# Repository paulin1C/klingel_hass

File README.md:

# klingel_hass
PCB and code for a small board that intercepts the bell wiring and allows muting and remote door opening with home assistant.
<br>
## hardware
### PCB
The gerber and drill files can be found in the `kicad` folder.<br>

### bill of materials
The following parts are used to assemble the PCB:
|reference|part name|value|package|
|---|---|---|---|
|C1-C5|capacitor|10 µF|smd 0805|
|D3,D4|bridge rectifier|ABS10|smd|
|D5,D11|red led||smd 0805|
|D1,D2,D6|diode|1N4007|tht DO-41|
|D7-D10|ws2812 led||smd|
|J1,J3|screw terminal|3 pins|tht 5.08 mm spacing|
|J2,J4,J5,J6|screw terminal|2 pins|tht 5.08 mm spacing|
|K1-K3|relay|5V SPDT|tht|
|Q1-Q3|transistor|BC547|tht TO-92|
|R2,R7,R8,R9,R12|resistor|1K|smd 0805|
|R1,R3,R4|resistor|10K|smd 0805|
|R5,R6|resistor|5|smd 0805|
|U1,U2|voltage regulator|AMS1117-1.5|smd SOT-223-3|
|U3|WEMOS D1 mini||tht|
|U4,U5|optocoupler|PC817|tht|

### connections
If you want to use the muting feature, you will have to cut the wires to your bell.
The voltage of your bell should be between 4V and 16V AC or DC.
A door opener could be connected to one of the relays.
|terminal name|description|
|----|----|
|5V|your 5V power supply (min. 1A)|
|bell-in|wires that normally supply power to your bell|
|bell-out|wires going to your bell|
|sense|additional input to detect voltage (4-16V AC or DC)|
|relayA,B|relay (NC = normally closes, NO = normally open)|

## software
I used esphome as a simple way to use the device with home assistant.

### configuration
Just change into the esphome directory, copy `secrets_example.yaml` to `secrets.yaml` and change its options accordingly.

### firmware upload
The firmware needs to be compiled with `esphome klingel_hass.yaml compile` and uploaded to a connected WEMOS D1 mini board with `esphome klingel_hass.yaml upload`.

### auto mute
A friend was worried about what would happen, when the device looses connection or gets stuck in a boot loop, while the bell was muted. So when auto mute is enabled, the bell stays connected/unmuted until a ring is detected and is only separating the bell connection, when the bell should be ringing. Depending on your bell, you might still hear a short ring until the relay opens.

## home assistant
The device should connect to wifi and be discovered by home assistant, which will ask you for the api password in `esphome/secrets.yaml` to connect.
<br>

### entities
|name|description|
|---|---|
|bell|changes to `on` when the bell is or should be ringing|
|sense|changes to `on` when a voltage is detected on the sense input|
|mute|mutes the bell when switched on|
|relayA|controls relay A|
|relayB|controls relay B|
|auto mute|controls auto mute feature|
|led|controls the small red led on the left|
|ws28|should control the ws2812 leds (untested)|

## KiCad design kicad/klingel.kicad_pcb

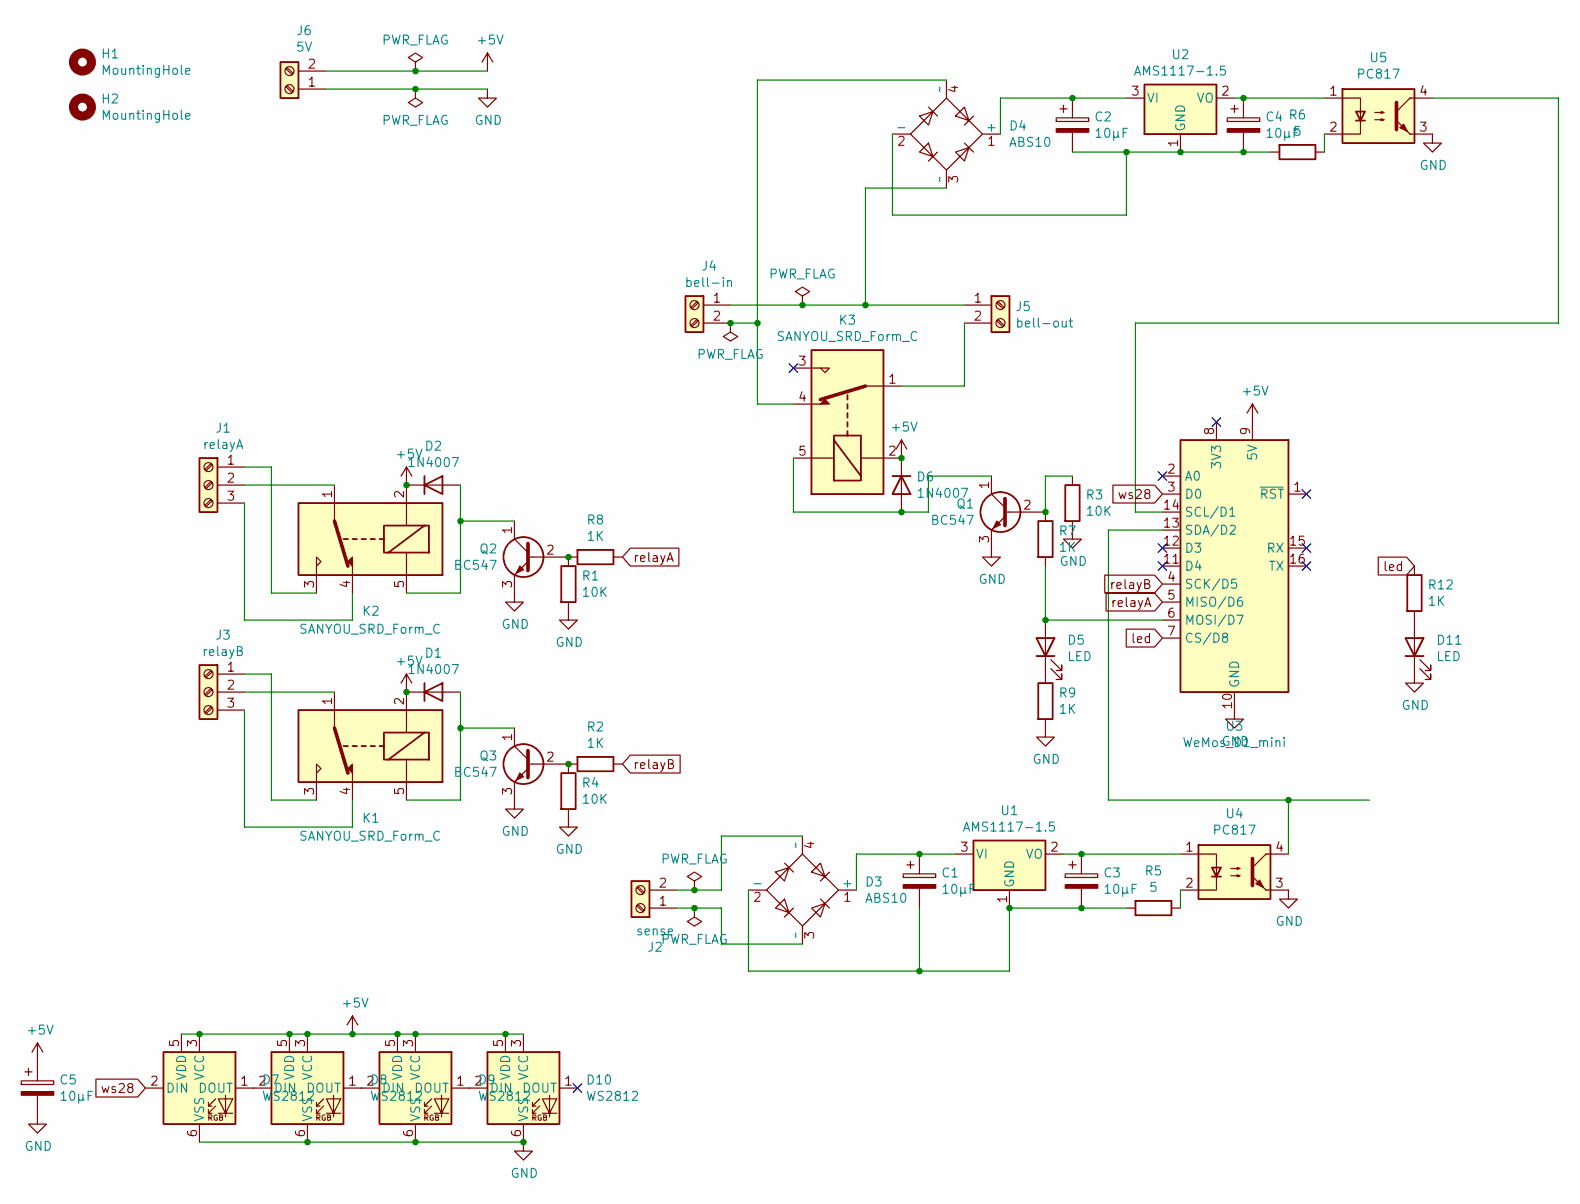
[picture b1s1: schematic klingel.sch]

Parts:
C1, C2, C3, C4, C5: 10µF; CP_EIA-3216-18_Kemet-A_Pad1.58x1.35mm_HandSolder
D1, D2, D6: 1N4007; D_DO-41_SOD81_P10.16mm_Horizontal
D3, D4: ABS10; Diode_Bridge_Diotec_ABS
D5, D11: LED; LED_0805_2012Metric
D7, D8, D9, D10: WS2812; LED_WS2812_PLCC6_5.0x5.0mm_P1.6mm
H1, H2: MountingHole; MountingHole_4.3mm_M4
J1: relayA; terminal_3pin
J2: sense; termina_2pin
J3: relayB; terminal_3pin
J4: bell-in; termina_2pin
J5: bell-out; termina_2pin
J6: 5V; termina_2pin
K1, K2, K3: SANYOU_SRD_Form_C; Relay_SPDT_SANYOU_SRD_Series_Form_C
Q1, Q2, Q3: BC547; TO-92_Inline
R1, R3, R4: 10K; R_0805_2012Metric_Pad1.20x1.40mm_HandSolder
R2, R7, R8, R9, R12: 1K; R_0805_2012Metric_Pad1.20x1.40mm_HandSolder
R5, R6: 5; R_0805_2012Metric_Pad1.20x1.40mm_HandSolder
U1, U2: AMS1117-1.5; SOT-223-3_TabPin2
U3: WeMos_D1_mini; WEMOS_D1_mini_light
U4, U5: PC817; DIP-4_W7.62mm

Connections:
+5V: C5.1, D1.1 (K), D2.1 (K), D6.1 (K), D7.3 (VCC), D7.5 (VDD), D8.3 (VCC), D8.5 (VDD), D9.3 (VCC), D9.5 (VDD), D10.3 (VCC), D10.5 (VDD), J6.2, K1.2, K2.2, K3.2, U3.9 (5V)
GND: C5.2, D7.6 (VSS), D8.6 (VSS), D9.6 (VSS), D10.6 (VSS), D11.1 (K), J6.1, Q1.3 (E), Q2.3 (E), Q3.3 (E), R1.2, R3.2, R4.2, R9.2, U3.10 (GND), U4.3, U5.3
unnamed: C1.1, D3.1 (+), U1.3 (VI)
unnamed: C1.2, C3.2, D3.2 (-), R5.2, U1.1 (GND)
unnamed: C2.1, D4.1 (+), U2.3 (VI)
unnamed: C2.2, C4.2, D4.2 (-), R6.2, U2.1 (GND)
unnamed: C3.1, U1.2 (VO), U4.1
unnamed: C4.1, U2.2 (VO), U5.1
unnamed: D1.2 (A), K1.5, Q3.1 (C)
unnamed: D2.2 (A), K2.5, Q2.1 (C)
unnamed: D3.3 (~~), J2.1
unnamed: D3.4 (~~), J2.2
unnamed: D4.3 (~~), J4.1, J5.1
unnamed: D4.4 (~~), J4.2, K3.4
unnamed: D5.1 (K), R9.1
unnamed: D5.2 (A), R7.2, U3.6 (MOSI/D7)
unnamed: D6.2 (A), K3.5, Q1.1 (C)
unnamed: D7.1 (DOUT), D8.2 (DIN)
unnamed: D8.1 (DOUT), D9.2 (DIN)
unnamed: D9.1 (DOUT), D10.2 (DIN)
unnamed: D11.2 (A), R12.2
unnamed: J1.1, K2.3
unnamed: J1.2, K2.1
unnamed: J1.3, K2.4
unnamed: J3.1, K1.3
unnamed: J3.2, K1.1
unnamed: J3.3, K1.4
unnamed: J5.2, K3.1
unnamed: Q1.2 (B), R3.1, R7.1
unnamed: Q2.2 (B), R1.1, R8.2
unnamed: Q3.2 (B), R2.2, R4.1
unnamed: R5.1, U4.2
unnamed: R6.1, U5.2
unnamed: U3.13 (SDA/D2), U4.4
unnamed: U3.14 (SCL/D1), U5.4
led: R12.1, U3.7 (CS/D8)
relayA: R8.1, U3.5 (MISO/D6)
relayB: R2.1, U3.4 (SCK/D5)
ws28: D7.2 (DIN), U3.3 (D0)

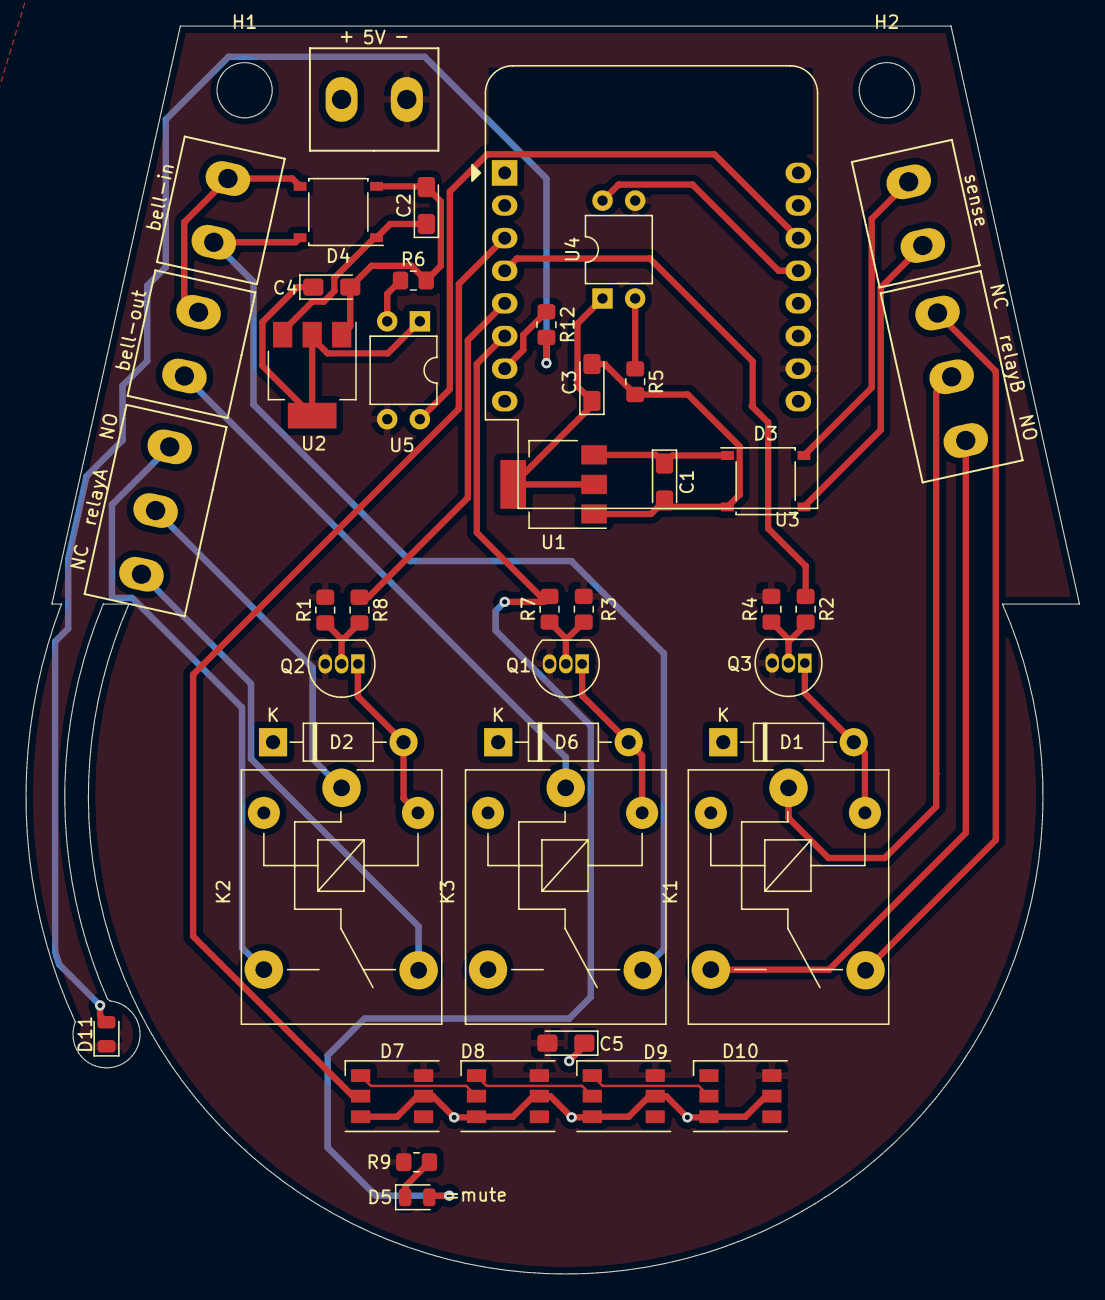
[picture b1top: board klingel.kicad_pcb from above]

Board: 2 copper layers, 82.0 x 97.2 mm, 45 parts (0 on the bottom side), 39 nets.

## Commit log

2021-02-19 fix typo
2021-02-19 add test setup picture
2021-02-19 add pictures to readme
2022-02-03 filter bell input
2022-02-03 Ensure door opener shuts off again
    We've had an incident, where the homeassistant script didn't complete or
    something along those lines, resulting in the door opener running for an
    hour or so. This change makes sure that the ESP itself turns off that
    pin after 10 seconds.
